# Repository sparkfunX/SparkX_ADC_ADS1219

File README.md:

SparkX Qwiic ADC ADS1219 - 24-Bit 4-Channel
========================================

[*SparkX Qwiic 24-Bit ADC - 4-Channel ADS1219 (SPX-23455)*](https://www.sparkfun.com/products/23455)

Qwiic breakout board for the ADS1219 4-channel 24-bit ADC from TI.

A lot of the time you just need to add more analog inputs to solve a problem. It happens. The SparkX Qwiic 24-Bit ADC can provide four channels of I<sup>2</sup>C controlled ADC input to your Qwiic enabled project. These channels can be used as single-ended inputs, or in pairs for differential inputs, running at sample rates of up to 1kHz. What makes this ADC even more powerful is that it has a programmable x1 or x4 gain amplifier that lets you "zoom in" on a very small change in analog voltage (but will still effect your input range and resolution). Utilizing our handy Qwiic system, it is easy to connect it to the rest of your system. However, we have broken out 0.1"-spaced pads too in case you prefer to use a breadboard. The analog inputs and reference pins are all broken out on 0.1"-spaced pads too. This board does not have screw terminals - there was not enough room!

The ADS1219 can use its own internal 2.048V voltage reference for measurements, or you can provide your own reference via the REFP and REFN breakout pads. You can also provide your own VDDA (AVDD) by opening the jumper and connecting a voltage to the VDDA pad. This ADC board has eight address jumpers that let you choose one of sixteen unique addresses (0x40 to 0x4F). With these, you can connect up to sixteen of these on the same I<sup>2</sup>C bus and have 64 channels of ADC. The maximum resolution of the converter is 24-bits, corresponding to 244.14nV per count at a gain of x1. At a gain of x4, the resolution is 61.04nV per count. Note: the _effective_ resolution is limited to 20-bits.

Repository Contents
-------------------

* [**/Documents**](./Documents/) - TI datasheet
* [**/Hardware**](./Hardware/) - KiCad design files (_pcb, _sch), Schematic (PDF)
* [**/Hardware/Production**](./Hardware/Production/) - Production panel files (_pcb, gerbers)
* [**/Production_Test**](./Production_Test/) - The Arduino sketch we use to test the board

Documentation
--------------

* [**Arduino Library**](https://github.com/sparkfun/SparkFun_ADS1219_Arduino_Library) - Arduino library for the ADS1219.

License Information
-------------------

This product is _**open source**_! 

Please review the LICENSE.md file for license information. 

If you have any questions or concerns on licensing, please visit the [SparkFun Forum](https://forum.sparkfun.com/viewforum.php?f=152) and post a topic. For more specific questions about this board, please visit this section of the forum: [SparkFun Forums: SparkX](https://forum.sparkfun.com/viewforum.php?f=123)

Distributed as-is; no warranty is given.

- Your friends at SparkFun.

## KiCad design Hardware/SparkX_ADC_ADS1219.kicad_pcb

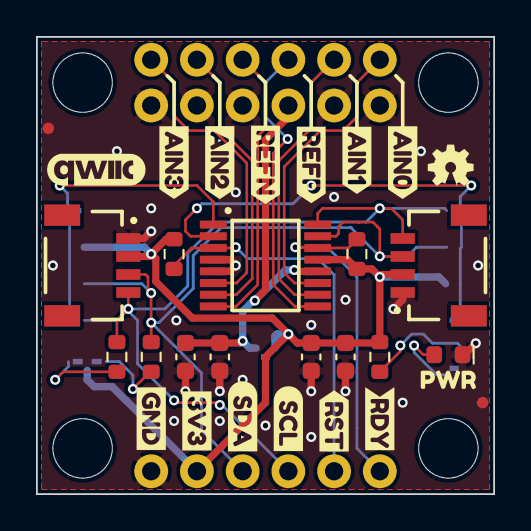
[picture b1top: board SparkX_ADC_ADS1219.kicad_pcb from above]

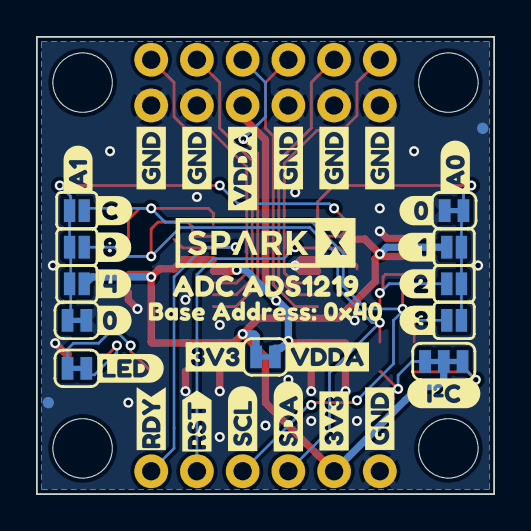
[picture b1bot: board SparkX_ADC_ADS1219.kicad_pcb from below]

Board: 2 copper layers, 25.4 x 25.4 mm, 79 parts (41 on the bottom side), 19 nets.

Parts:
C1, C3: 2.2uF; C_0603_1608Metric
C2, C4: 0.1uF_0603_25V_20%; C_0603_1608Metric
D1: Red; LED_0603_1608Metric
FID1, FID2, FID3, FID4: Fiducial_0.635; Fiducial_0.635mm
J1, J2: Qwiic_RA; JST04_1MM_RA
J3, J4: Conn_01x06; 1X06
J5: Conn_01x02; 1X02
J6: I2C_01x04; 1X04
JP1, JP2, JP4, JP8: SMT-JUMPER_2_NC_TRACE_SILK
JP3: SMT-JUMPER_3_2-NC_TRACE_SILK
JP5, JP6, JP7, JP9, JP10, JP11: SMT-JUMPER_2_NO_SILK
R1: 1k; R_0603_1608Metric
R2, R3: 2.2k; R_0603_1608Metric
R4, R5: 10k; R_0603_1608Metric
Ref**: Val**; OSHW-LOGO-MINI
ST1, ST2, ST3, ST4: Stand_off; STAND-OFF
U1: ADS1219IPW; TSSOP-16
U2: ORDERING_INSTRUCTIONS
kibuzzard-64C3B30F: G***; kibuzzard-64C3B30F
kibuzzard-64C3BD7A: G***; kibuzzard-64C3BD7A
kibuzzard-64C36D1A: G***; kibuzzard-64C36D1A
kibuzzard-64C36D2D: G***; kibuzzard-64C36D2D
kibuzzard-64C36D5B: G***; kibuzzard-64C36D5B
kibuzzard-64C36D6C: G***; kibuzzard-64C36D6C
kibuzzard-64C36D47: G***; kibuzzard-64C36D47
kibuzzard-64C36D91: G***; kibuzzard-64C36D91
kibuzzard-64C36E7A, kibuzzard-64C36E7A#2, kibuzzard-64C36E7A#3, kibuzzard-64C36E7A#4, kibuzzard-64C36E7A#5, kibuzzard-64C36E7A#6, kibuzzard-64C36E7A#7: G***; kibuzzard-64C36E7A
kibuzzard-64C36EF5: G***; kibuzzard-64C36EF5
kibuzzard-64C37A88, kibuzzard-64C37A88#2, kibuzzard-64C37A88#3: G***; kibuzzard-64C37A88
kibuzzard-64C37AD1: G***; kibuzzard-64C37AD1
kibuzzard-64C37B2E: G***; kibuzzard-64C37B2E
kibuzzard-64C37B4E: G***; kibuzzard-64C37B4E
kibuzzard-64C37B05: G***; kibuzzard-64C37B05
kibuzzard-64C37B97: G***; kibuzzard-64C37B97
kibuzzard-64C37BC1: G***; kibuzzard-64C37BC1
kibuzzard-64C37BF9: G***; kibuzzard-64C37BF9
kibuzzard-64C37C5C: G***; kibuzzard-64C37C5C
kibuzzard-64C37C16: G***; kibuzzard-64C37C16
kibuzzard-64C37CC9: G***; kibuzzard-64C37CC9
kibuzzard-64C37D63: G***; kibuzzard-64C37D63
kibuzzard-64C37FAB: G***; kibuzzard-64C37FAB
kibuzzard-64C375B4: G***; kibuzzard-64C375B4
kibuzzard-64C375BE: G***; kibuzzard-64C375BE
kibuzzard-64C375C5: G***; kibuzzard-64C375C5
kibuzzard-64C375DA: G***; kibuzzard-64C375DA
kibuzzard-64C375F2: G***; kibuzzard-64C375F2
kibuzzard-64C3756D: G***; kibuzzard-64C3756D
kibuzzard-64C3761E: G***; kibuzzard-64C3761E
kibuzzard-64C37519: G***; kibuzzard-64C37519
kibuzzard-64C37614: G***; kibuzzard-64C37614
kibuzzard-64C38090: G***; kibuzzard-64C38090

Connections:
+3.3V: C1.1, C2.1, J1.2, J2.2, J6.2, JP1.1 (A), JP3.2 (C), JP5.2 (B), JP9.2 (B), R1.1, R4.1, R5.1, U1.13 (DVDD)
A0: JP4.1 (A), JP5.1 (A), JP6.1 (A), JP7.1 (A), U1.1 (A0)
A1: JP8.1 (A), JP9.1 (A), JP10.1 (A), JP11.1 (A), U1.2 (A1)
AIN0: J3.6, U1.11 (AIN0)
AIN1: J3.5, U1.10 (AIN1)
AIN2: J3.2, U1.7 (AIN2)
AIN3: J3.1, U1.6 (AIN3)
GND: C1.2, C2.2, C3.2, C4.2, D1.1 (K), J1.1, J2.1, J4.1, J4.2, J4.3, J4.5, J4.6, J6.1, JP4.2 (B), JP8.2 (B), U1.4 (DGND), U1.5 (AGND)
unnamed: D1.2 (A), JP2.1 (A)
unnamed: JP2.2 (B), R1.2
unnamed: JP3.1 (A), R3.1
unnamed: JP3.3 (B), R2.1
REFN: J3.3, U1.8 (REFN)
REFP: J3.4, U1.9 (REFP)
SCL: J1.4, J2.4, J6.4, JP7.2 (B), JP11.2 (B), R2.2, U1.16 (SCL)
SDA: J1.3, J2.3, J6.3, JP6.2 (B), JP10.2 (B), R3.2, U1.15 (SDA)
VDDA: C3.1, C4.1, J4.4, JP1.2 (B), U1.12 (AVDD)
~DRDY: J5.2, R4.2, U1.14 (~DRDY)
~RESET: J5.1, R5.2, U1.3 (~RESET)

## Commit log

2023-07-27 Very work-in-progress
2023-07-28 Routed
2023-07-28 Rename everything
2023-09-06 Add panel
2023-12-13 Add datasheet
2023-12-13 Add README and LICENSE
2023-12-15 Add product image
